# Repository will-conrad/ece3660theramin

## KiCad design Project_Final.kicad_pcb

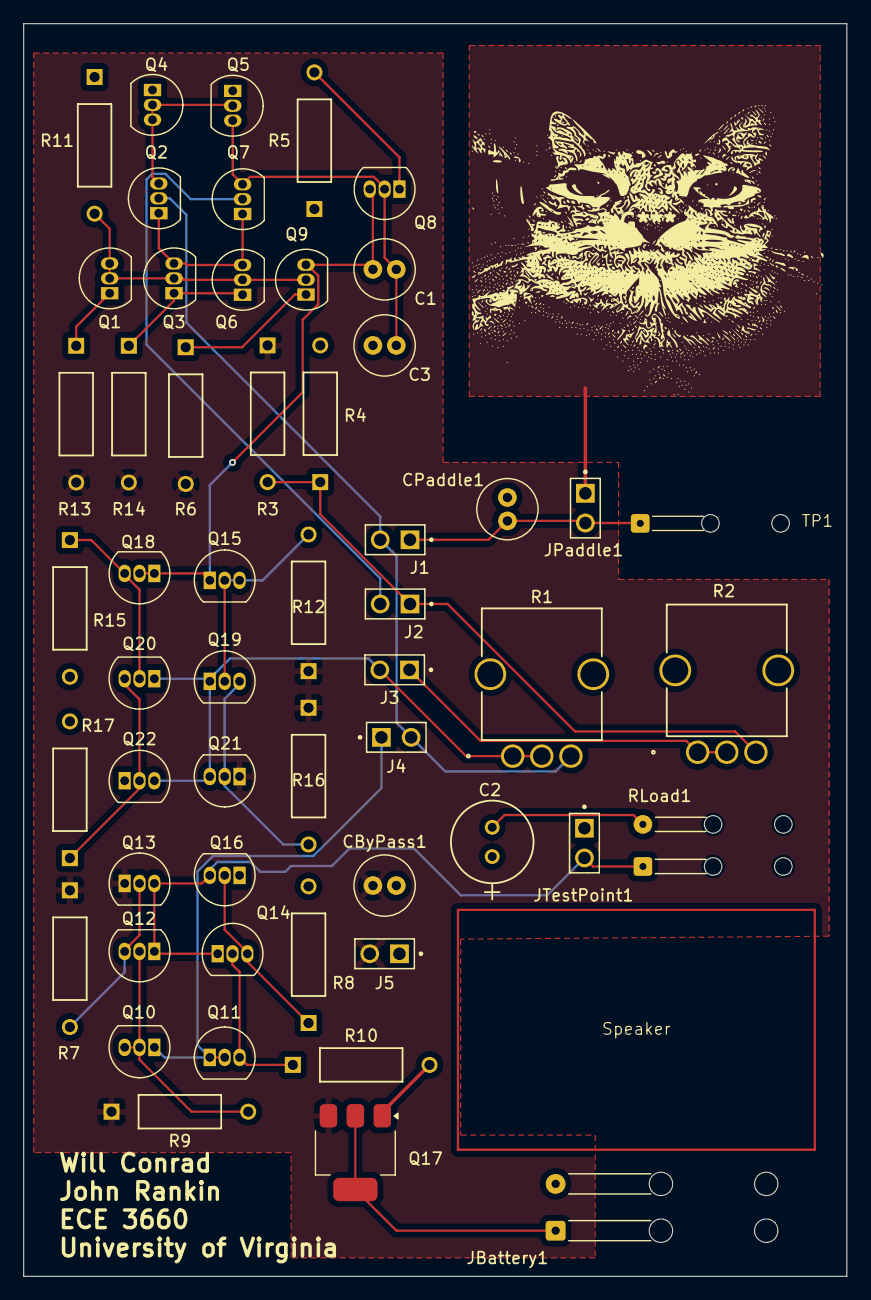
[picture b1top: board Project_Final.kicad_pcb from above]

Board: 2 copper layers, 70.4 x 107.1 mm, 54 parts (0 on the bottom side), 29 nets.

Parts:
C1, C3: C; C_Radial_D5.0mm_H11.0mm_P2.00mm
C2: 35ZLH100MEFC6.3X11; CAP_YX_6P3X11_RUB
CByPass1: C; C_Radial_D5.0mm_H11.0mm_P2.00mm
CPaddle1: C; C_Radial_D5.0mm_H11.0mm_P2.00mm
J1, J2, J3, J4, J5: Conn_01x02_Pin; HARWIN_M20-9990246
JBattery1: Conn_01x02_Pin; SolderWire-0.15sqmm_1x02_P4mm_D0.5mm_OD1.5mm_Relief2x
JPaddle1: Conn_01x02_Pin; HARWIN_M20-9990246
JTestPoint1: Conn_01x02_Pin; HARWIN_M20-9990246
Q1, Q2, Q3, Q6, Q7, Q9, Q10, Q12, Q15, Q16, Q19, Q22: 2N3906; TO-92_Inline
Q4, Q5, Q8, Q11, Q13, Q14, Q18, Q20, Q21: 2N3904; TO-92_Inline
Q17: BSP89; SOT-223-3_TabPin2
R1: PTV09A-4015F-B103; PTV09A-4015F-B104_BRN
R2: PTV09A-4015F-B104; PTV09A-4015F-B104_BRN
R3, R4, R5, R6, R7, R8, R9, R10, R11, R12, R13, R14, R15, R16, R17: R; YAG_MF25_YAG
RLoad1: R; SolderWire-0.1sqmm_1x02_P3.6mm_D0.4mm_OD1mm_Relief2x
TP1: TestPoint; Single_Relief

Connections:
unnamed: C2.2, RLoad1.2
unnamed: CPaddle1.1, J1.1, JPaddle1.2, TP1.1
unnamed: J2.1, R2.3, R3.2, R4.1
unnamed: J3.1, R2.1, R2.2
unnamed: JBattery1.1, Q17.2 (D)
unnamed: Q1.2 (B), Q1.3 (C), Q3.2 (B), Q6.2 (B), Q9.2 (B), R11.2
unnamed: Q1.1 (E), R13.1
unnamed: Q2.3 (C), Q4.2 (B), Q4.3 (C), Q5.2 (B)
unnamed: Q2.1 (E), Q3.3 (C), Q6.3 (C), Q7.1 (E)
unnamed: Q3.1 (E), Q6.1 (E), R14.1
unnamed: C1.1, C3.1, Q5.3 (C), Q7.3 (C), Q8.2 (B)
unnamed: Q8.1 (E), R5.2
unnamed: Q9.1 (E), R6.1
unnamed: Q10.2 (B), Q10.3 (C), Q12.2 (B), R9.2
unnamed: Q11.3 (C), Q14.2 (B), R10.1
unnamed: Q12.3 (C), Q13.2 (B), R7.2
unnamed: Q14.3 (C), Q16.2 (B), R8.1
unnamed: Q15.2 (B), Q15.3 (C), Q19.2 (B), R12.2
unnamed: C1.2, Q8.3 (C), Q9.3 (C), Q15.1 (E), Q18.1 (E), Q18.2 (B)
unnamed: Q18.3 (C), Q20.2 (B), R15.1
unnamed: Q19.3 (C), Q21.2 (B), R16.2
unnamed: Q20.3 (C), Q22.2 (B), R17.1
V+: J2.2, Q7.2 (B)
V-: J1.2, J4.2, Q2.2 (B), R1.3
VCC: CByPass1.1, J5.2, Q13.1 (E), Q17.3 (S), Q21.1 (E), R3.1, R6.2, R7.1, R9.1, R12.1, R13.2, R14.2, R16.1
VEE: C2.1, C3.2, CByPass1.2, CPaddle1.2, J5.1, JBattery1.2, JPaddle1.1, JTestPoint1.1, Q4.1 (E), Q5.1 (E), Q16.1 (E), Q17.1 (G), Q22.1 (E), R4.2, R5.1, R8.2, R10.2, R11.1, R15.2, R17.2
V_In_Output: J4.1, Q10.1 (E), Q11.1 (E), Q11.2 (B)
V_Out_Op-Amp: J3.2, Q19.1 (E), Q20.1 (E), Q21.3 (C), Q22.3 (C), R1.1, R1.2
V_Out_Output: JTestPoint1.2, Q12.1 (E), Q13.3 (C), Q14.1 (E), Q16.3 (C), RLoad1.1

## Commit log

2025-11-21 first add
2025-11-22 update with john's copy
2025-11-22 starting new layout
    in progress
2025-11-22 edits. near final layout
2025-11-22 finished layout
2025-11-22 edit?
2025-11-22 finished
2025-11-22 fixed Errors
2025-11-22 udpated
2025-11-22 fixed planes
2025-12-07 updated values
